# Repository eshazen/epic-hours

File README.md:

# epic-hours

This is a project to create an electronic sign to display the opening
hours in EPIC.  Basic function is simple:  display open and close time
for each day of the week

There are (14) 8x24 matrix displays for open/close 7 days/week.
These use a special font to fit in the space:

    ten hours:   (blank) or 1
    one hours:   (blank) or 0-9
    ten minutes: (blank) or 0, 3
    one minutes: (blank) or 0

At the top there is a larger matrix, 8x64 which could display
a scrolling banner.

Each 8x8 matrix is driven by a MAX7219 controller IC.
See for example 
[documentation](https://lastminuteengineers.com/max7219-dot-matrix-arduino-tutorial/).

### LED version

The first version should just be "boring" LEDs.  Probably LED matrix,
at least for a banner at the top so messages can be scrolled.
8x8 maxtrix are very popular, so thinking of a 5x7 font.
24 columns work for 12:34 displays.

Need a total of 42+8 = 50 of these.  This is about $100
for modules with MAX7219 included.

Power, 3 digits, quiescent (blanked) = 20mA.

| Intensity | mA  |
|-----------|-----|
| 3         | 154 |
| 2         | 118 |
| 1         | 80  |

Say 17 groups of 3 @ 150mA = 2.6A @ 5V

Standoffs:

    8   8-32 x 1 inch
	200 6-32 x 1/2 inch less than 0.22" OD

[Preview](Sketches/amazon_8x8.jpg)

### Development Notes

A pcb [multi_display_shield] https://github.com/eshazen/epic-hours/tree/main/KiCAD/multi_display_shield provides power distribution and control for 8
displays.  Each day is organized as a 8x48 single display,
with an 8x64 banner at the top.

For Wifi:  propose to use an ESP32 30-pin dev board.  
See (this page)[https://lastminuteengineers.com/esp32-pinout-reference/]
for some very useful notes.

### Software / Interface

Use Arduino Uno as display controller.  Serial command set:

	T n hh:mm hh:mm   - Time - set weekday time (0,1 = Mon, 2,3 = Tue etc)
	                           for opening and closing
	M text...         - Banner - set banner text.  Scroll if too long
    I n               - Intensity - set intensity n=0-7

ESP32 connects to eduroam WiFi and handles queries such as:

http://10.239.25.67/CMD=M%20Welcome%20to%20EPIC

Everything after the "CMD=" is percent-decoded and sent to the Arduino.

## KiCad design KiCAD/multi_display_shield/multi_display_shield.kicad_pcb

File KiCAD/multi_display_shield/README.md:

# Multi-Display Shield

This is a very simple Arduino shield which allows driving of up to 8
LED displays based on the MAX7219 or similar SPI-based driver.
The board fans out `MOSI` and `SCK` to all boards using '244 drivers, and
provides separate `CS` signals to each.

## ECOs

* Jumper U1 pin 2-4

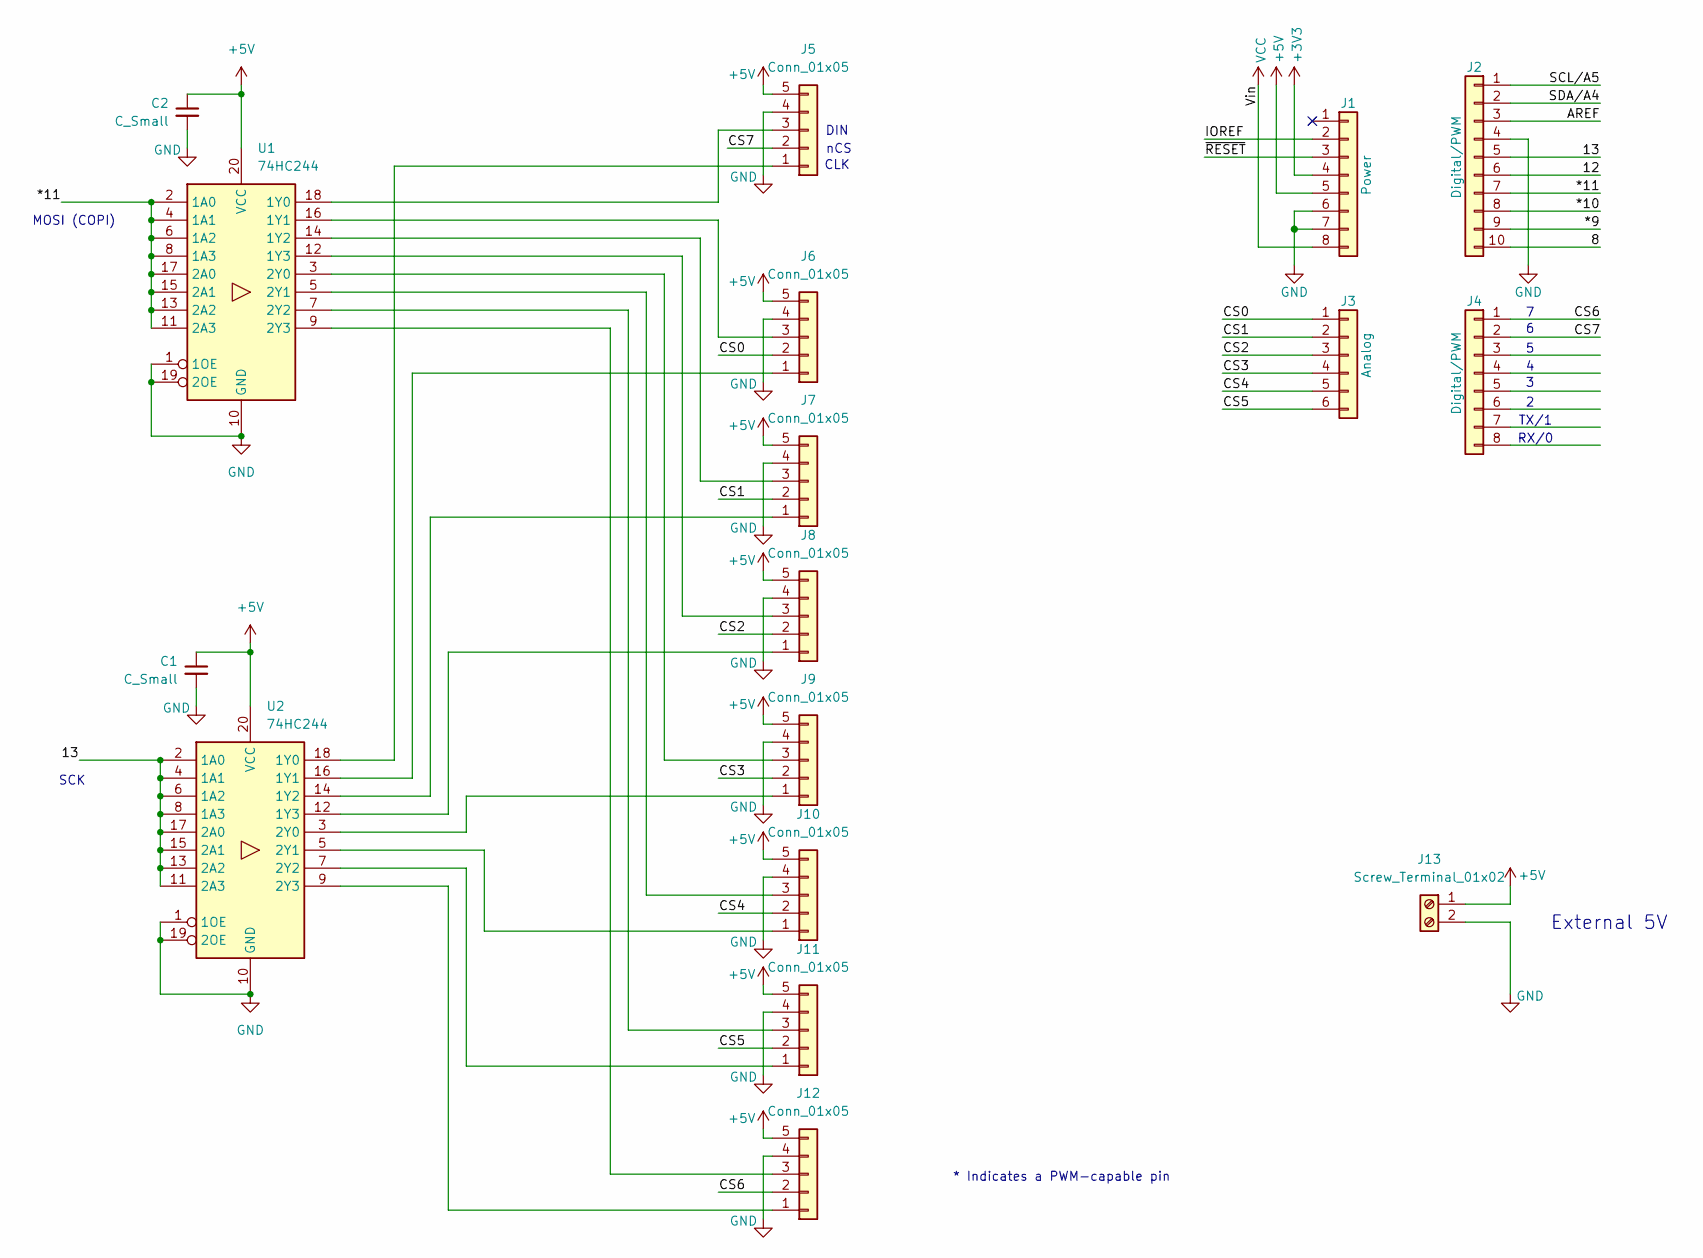
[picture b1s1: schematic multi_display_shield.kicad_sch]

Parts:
C1, C2: C_Small; C_Rect_L7.0mm_W2.5mm_P5.00mm
J1: Power; PinSocket_1x08_P2.54mm_Vertical
J2: Digital/PWM; PinSocket_1x10_P2.54mm_Vertical
J3: Analog; PinSocket_1x06_P2.54mm_Vertical
J4: Digital/PWM; PinSocket_1x08_P2.54mm_Vertical
J5, J6, J7, J8, J9, J10, J11, J12: Conn_01x05; PinHeader_1x05_P2.54mm_Vertical
J13: Screw_Terminal_01x02; Wago_734-132_1x02_P3.50mm_Vertical
U1, U2: 74HC244; DIP-20_W7.62mm

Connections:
+3V3: J1.4
+5V: C1.1, C2.1, J1.5, J5.5, J6.5, J7.5, J8.5, J9.5, J10.5, J11.5, J12.5, J13.1, U1.20 (VCC), U2.20 (VCC)
/8: J2.10
/12: J2.6
/13: J2.5, U2.2 (1A0), U2.4 (1A1), U2.6 (1A2), U2.8 (1A3), U2.11 (2A3), U2.13 (2A2), U2.15 (2A1), U2.17 (2A0)
/*9: J2.9
/*10: J2.8
/*11: J2.7, U1.2 (1A0), U1.4 (1A1), U1.6 (1A2), U1.8 (1A3), U1.11 (2A3), U1.13 (2A2), U1.15 (2A1), U1.17 (2A0)
/AREF: J2.3
/CS0: J3.1, J6.2
/CS1: J3.2, J7.2
/CS2: J3.3, J8.2
/CS3: J3.4, J9.2
/CS4: J3.5, J10.2
/CS5: J3.6, J11.2
/CS6: J4.1, J12.2
/CS7: J4.2, J5.2
/IOREF: J1.2
/SCL/A5: J2.1
/SDA/A4: J2.2
/~RESET: J1.3
GND: C1.2, C2.2, J1.6, J1.7, J2.4, J5.4, J6.4, J7.4, J8.4, J9.4, J10.4, J11.4, J12.4, J13.2, U1.1 (1OE), U1.10 (GND), U1.19 (2OE), U2.1 (1OE), U2.10 (GND), U2.19 (2OE)
unnamed: J5.1, U2.18 (1Y0)
unnamed: J5.3, U1.18 (1Y0)
unnamed: J6.1, U2.16 (1Y1)
unnamed: J6.3, U1.16 (1Y1)
unnamed: J7.1, U2.14 (1Y2)
unnamed: J7.3, U1.14 (1Y2)
unnamed: J8.1, U2.12 (1Y3)
unnamed: J8.3, U1.12 (1Y3)
unnamed: J9.1, U2.3 (2Y0)
unnamed: J9.3, U1.3 (2Y0)
unnamed: J10.1, U2.5 (2Y1)
unnamed: J10.3, U1.5 (2Y1)
unnamed: J11.1, U2.7 (2Y2)
unnamed: J11.3, U1.7 (2Y2)
unnamed: J12.1, U2.9 (2Y3)
unnamed: J12.3, U1.9 (2Y3)
VCC: J1.8

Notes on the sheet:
CLK
SCK
* Indicates a PWM-capable pin
RX/0
MOSI (COPI)
nCS
DIN
TX/1
External 5V

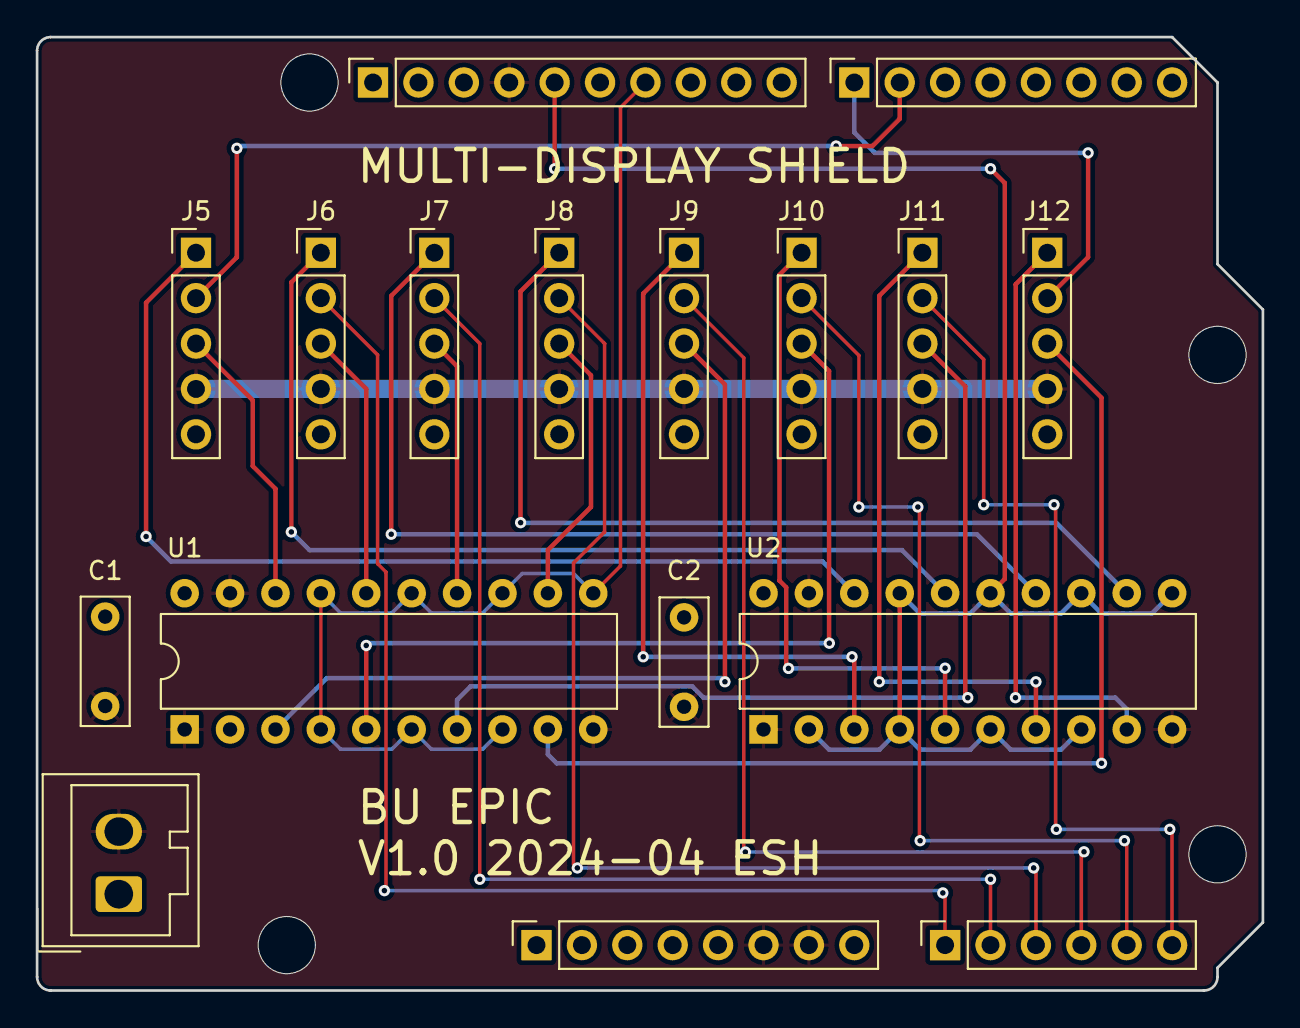
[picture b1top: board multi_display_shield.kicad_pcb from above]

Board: 2 copper layers, 68.6 x 53.3 mm, 21 parts (0 on the bottom side), 28 nets.

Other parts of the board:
MH1, MH2, MH3, MH4: MountingHole_3.2mm

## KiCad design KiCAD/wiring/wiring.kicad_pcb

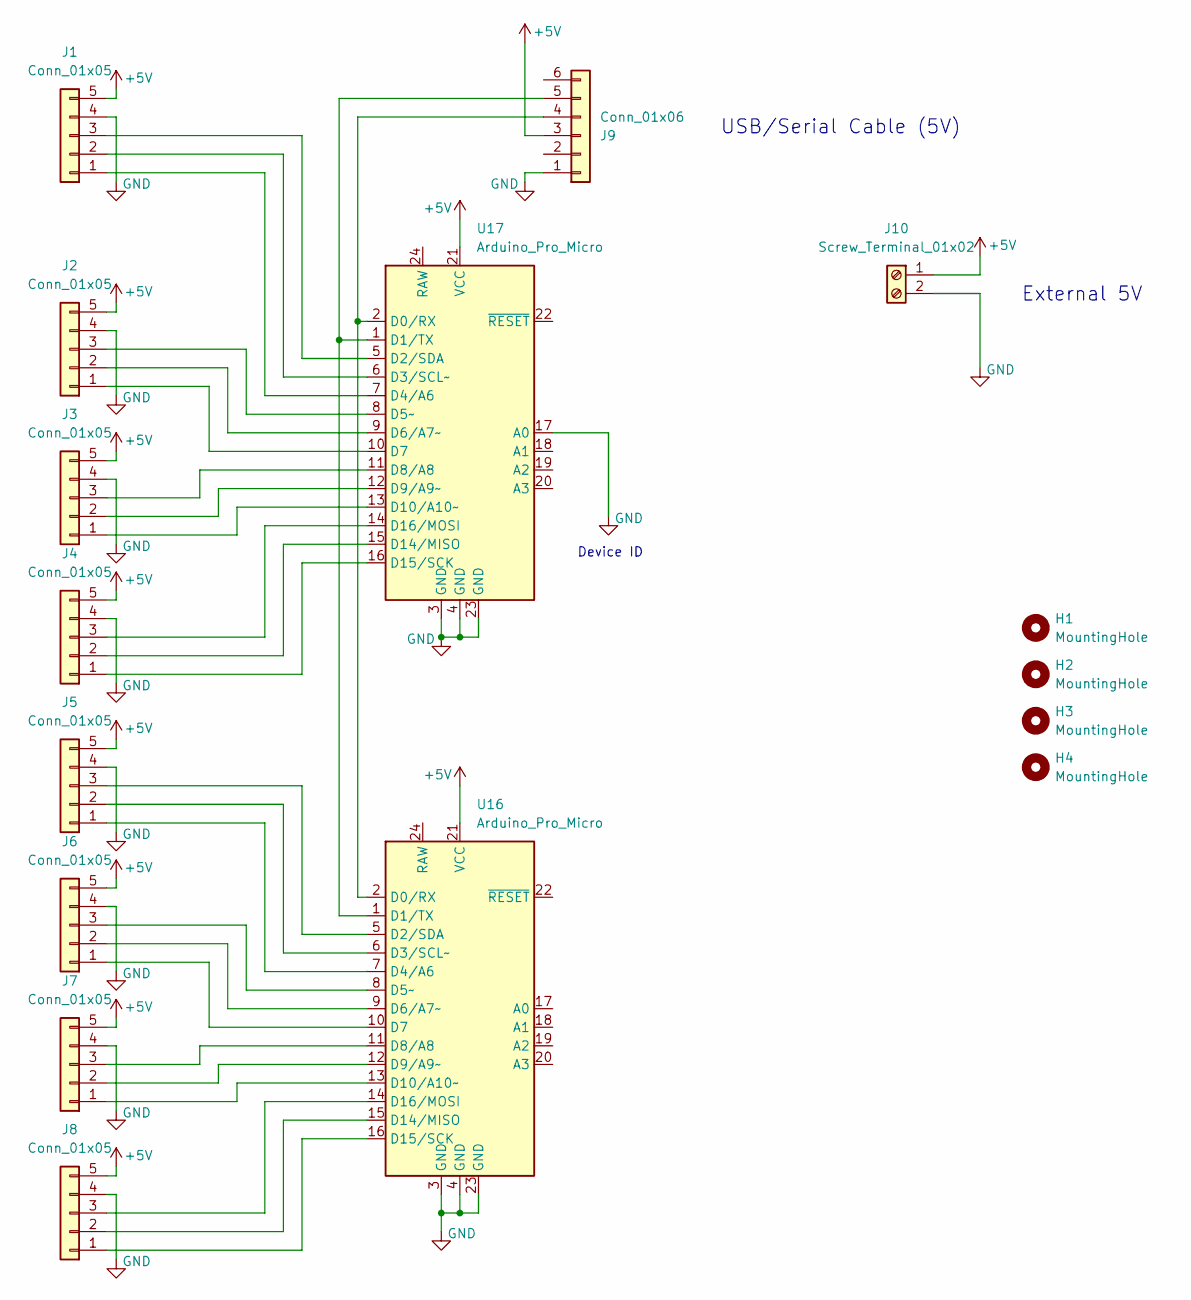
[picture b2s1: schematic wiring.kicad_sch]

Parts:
H1, H2, H3, H4: MountingHole; MountingHole_4.3mm_M4
J1, J2, J3, J4, J5, J6, J7, J8: Conn_01x05; PinHeader_1x05_P2.54mm_Vertical
J9: Conn_01x06; PinHeader_1x06_P2.54mm_Vertical
J10: Screw_Terminal_01x02; Wago_734-132_1x02_P3.50mm_Vertical
U16, U17: Arduino_Pro_Micro; DIP-24_W15.24mm_LongPads

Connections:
+5V: J1.5, J2.5, J3.5, J4.5, J5.5, J6.5, J7.5, J8.5, J9.3, J10.1, U16.21 (VCC), U17.21 (VCC)
GND: J1.4, J2.4, J3.4, J4.4, J5.4, J6.4, J7.4, J8.4, J9.1, J10.2, U16.3 (GND), U16.4 (GND), U16.23 (GND), U17.3 (GND), U17.4 (GND), U17.17 (A0), U17.23 (GND)
unnamed: J1.1, U17.7 (D4/A6)
unnamed: J1.2, U17.6 (D3/SCL~)
unnamed: J1.3, U17.5 (D2/SDA)
unnamed: J2.1, U17.10 (D7)
unnamed: J2.2, U17.9 (D6/A7~)
unnamed: J2.3, U17.8 (D5~)
unnamed: J3.1, U17.13 (D10/A10~)
unnamed: J3.2, U17.12 (D9/A9~)
unnamed: J3.3, U17.11 (D8/A8)
unnamed: J4.1, U17.16 (D15/SCK)
unnamed: J4.2, U17.15 (D14/MISO)
unnamed: J4.3, U17.14 (D16/MOSI)
unnamed: J5.1, U16.7 (D4/A6)
unnamed: J5.2, U16.6 (D3/SCL~)
unnamed: J5.3, U16.5 (D2/SDA)
unnamed: J6.1, U16.10 (D7)
unnamed: J6.2, U16.9 (D6/A7~)
unnamed: J6.3, U16.8 (D5~)
unnamed: J7.1, U16.13 (D10/A10~)
unnamed: J7.2, U16.12 (D9/A9~)
unnamed: J7.3, U16.11 (D8/A8)
unnamed: J8.1, U16.16 (D15/SCK)
unnamed: J8.2, U16.15 (D14/MISO)
unnamed: J8.3, U16.14 (D16/MOSI)
unnamed: J9.4, U16.2 (D0/RX), U17.2 (D0/RX)
unnamed: J9.5, U16.1 (D1/TX), U17.1 (D1/TX)

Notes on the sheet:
Device ID
External 5V
USB/Serial Cable (5V)

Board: 2 copper layers, 16 parts (0 on the bottom side), 28 nets, no tracks yet.

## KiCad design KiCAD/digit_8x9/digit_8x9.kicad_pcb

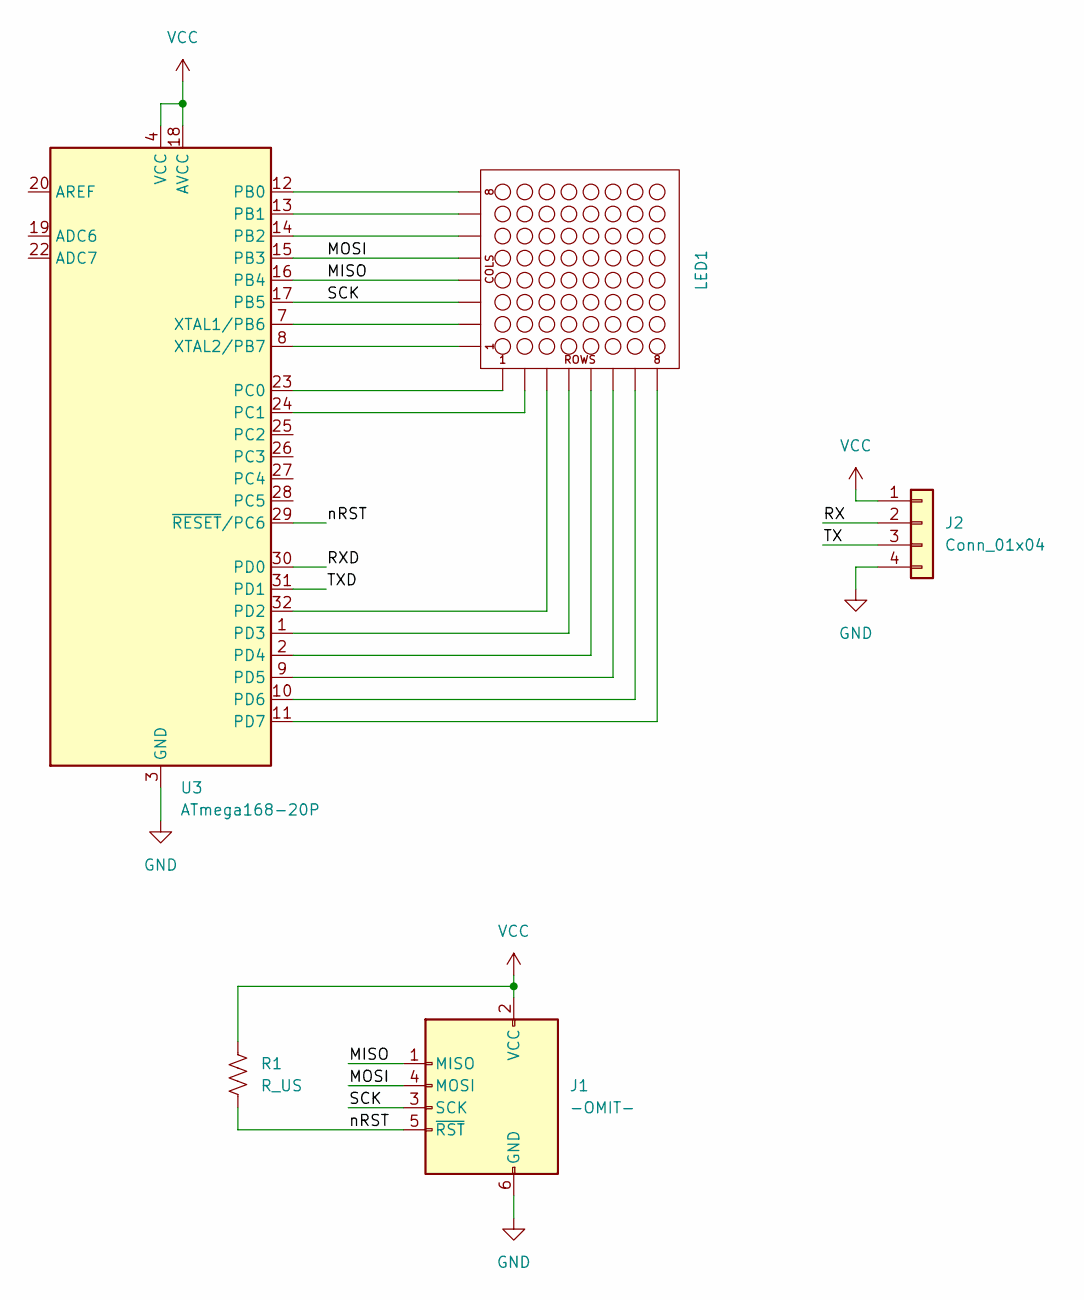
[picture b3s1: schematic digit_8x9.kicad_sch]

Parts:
J1: -OMIT-; PinHeader_2x03_P2.54mm_Vertical
J2: Conn_01x04; PinHeader_1x04_P2.54mm_Vertical
LED1: Adafruit_32mm_8x8
R1: R_US; R_0805_2012Metric_Pad1.20x1.40mm_HandSolder
U3: ATmega168-20P; TQFP-32_7x7mm_P0.8mm

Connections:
/MISO: J1.1 (MISO), LED1.10 (COL4), U3.16 (PB4)
/MOSI: J1.4 (MOSI), LED1.6 (COL5), U3.15 (PB3)
/RX: J2.2
/RXD: U3.30 (PD0)
/SCK: J1.3 (SCK), LED1.4 (COL3), U3.17 (PB5)
/TX: J2.3
/TXD: U3.31 (PD1)
/nRST: J1.5 (~RST), R1.2, U3.29 (~RESET/PC6)
GND: J1.6 (GND), J2.4, U3.3 (GND), U3.5 (GND), U3.21 (GND)
unnamed: LED1.13 (COL1), U3.8 (XTAL2/PB7)
unnamed: LED1.3 (COL2), U3.7 (XTAL1/PB6)
unnamed: LED1.11 (COL6), U3.14 (PB2)
unnamed: LED1.15 (COL7), U3.13 (PB1)
unnamed: LED1.16 (COL8), U3.12 (PB0)
unnamed: LED1.9 (ROW1), U3.23 (PC0)
unnamed: LED1.14 (ROW2), U3.24 (PC1)
unnamed: LED1.8 (ROW3), U3.32 (PD2)
unnamed: LED1.12 (ROW4), U3.1 (PD3)
unnamed: LED1.1 (ROW5), U3.2 (PD4)
unnamed: LED1.7 (ROW6), U3.9 (PD5)
unnamed: LED1.2 (ROW7), U3.10 (PD6)
unnamed: LED1.5 (ROW8), U3.11 (PD7)
VCC: J1.2 (VCC), J2.1, R1.1, U3.4 (VCC), U3.6 (VCC), U3.18 (AVCC)

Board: 2 copper layers, 5 parts (4 on the bottom side), 19 nets, no tracks yet.

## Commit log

2024-02-08 initial readme
2024-02-12 notes
2024-02-13 multi-digit prototype
2024-03-01 readme
2024-03-02 starting on schematic
2024-03-02 schematic work
2024-03-02 Atmega version
2024-03-03 Arduino test for 8x24 matrix
2024-03-06 working on drawing
2024-03-07 drawings
2024-03-11 updated board holder
2024-03-23 update holder
2024-04-19 Wiring
2024-04-19 multi-display shield board
2024-05-08 working on software
2024-05-10 Add gerbers as built, update README
2024-07-10 first version remote control
2024-07-11 fixing conflict
2024-07-11 software and box
2024-07-18 software
2024-07-22 create perl script to setup sign
2024-07-23 temporary control CGI script (works on ohm)
2024-07-23 Clean up laser cut files
2025-08-05 add new box, update software
